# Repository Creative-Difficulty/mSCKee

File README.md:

# mSCKee

| | |
|-|-|

__msCKee__ is an open source split Keyboard with per-key white backlighting, and two light sensors, adapting to ambient brightness.

It features:
- dimmable white backlighting for every key, programmable to display animations
- two light sensors (one per side) to automatically dim backlight
- Integrated RP2040 MCU IC
- Minimalist aluminium enclosure
- USB-C 2.0 connectivity
- 4 layer board: Signal - GND - 3,3V and 5V split pour - Signal
- RJ9 cable connection between halves
- Cherry MX 5 pin switch compatible

All manufacturing and part costs were covered by Hack Club through their Outpost program (<https://outpost.hackclub.com>), which I am very grateful for.

Keycaps are custom from Hack Club for Outpost, product photos (top of the README) were taken in Vienna, Austria.

## BOM

The JLC BOM covers the majority of expenses:

Total cost of JLCPCB(A):

| Description | Price/Piece | Total Price | Purchase link | Justification |
|---|---|---|---|---|
| JLCPCB manufacturing and PCB assembly | 124.05€ + 22.72€ shipping | 146.77€ | | |
| Cherry MX Red Switch kit | 17.99€ + 11.99€ shipping | 29.98€ | https://shop.cherry.de/cherry-mx2a-rgb-red-switch-kit.html | |
| SP3T Switch: PCM13SMTR | 0.82€ | 5×0.82€ + 5.90€ shipping + 20% VAT = 12€ | https://www.tme.eu/at/details/pcm13smtr/schiebeschalter/c-k/ | No equivalent SP3T switch is available at JLC |
| 1N4148W7F DII SOD-123 diode | 0.05€ | 36×0.05€ + 6.95€ shipping + 20% VAT = 10.5€ | https://www.reichelt.com/at/en/shop/product/small-signal_switching_diode_100_v_300_ma_sod-123-219381 | Diodes for key matrix, mounted on back side of PCB, so not assembled or provided by JLC |
| **Total** | | **199.25€** | | |
| **Total (USD)** | | **232.59USD** | | |

## PCB & schematic images

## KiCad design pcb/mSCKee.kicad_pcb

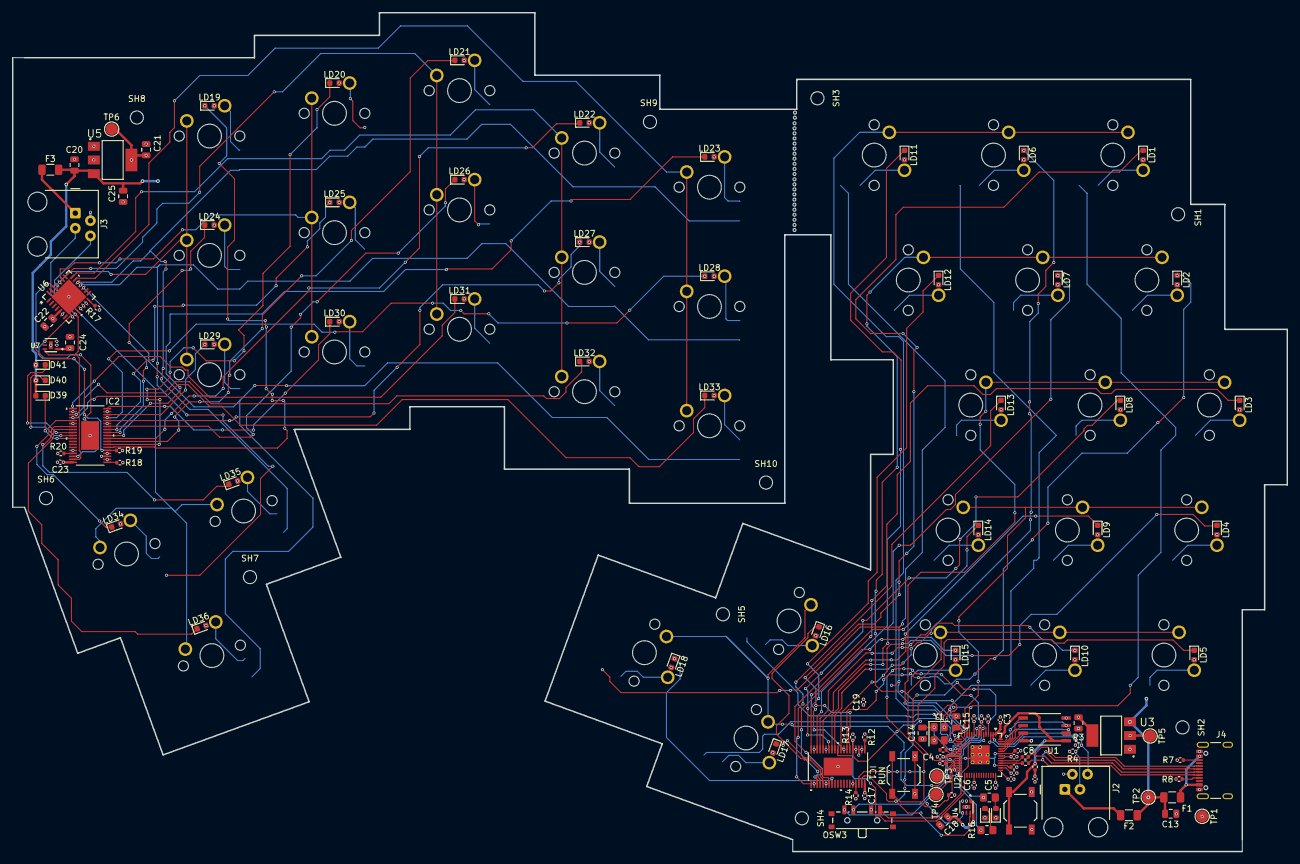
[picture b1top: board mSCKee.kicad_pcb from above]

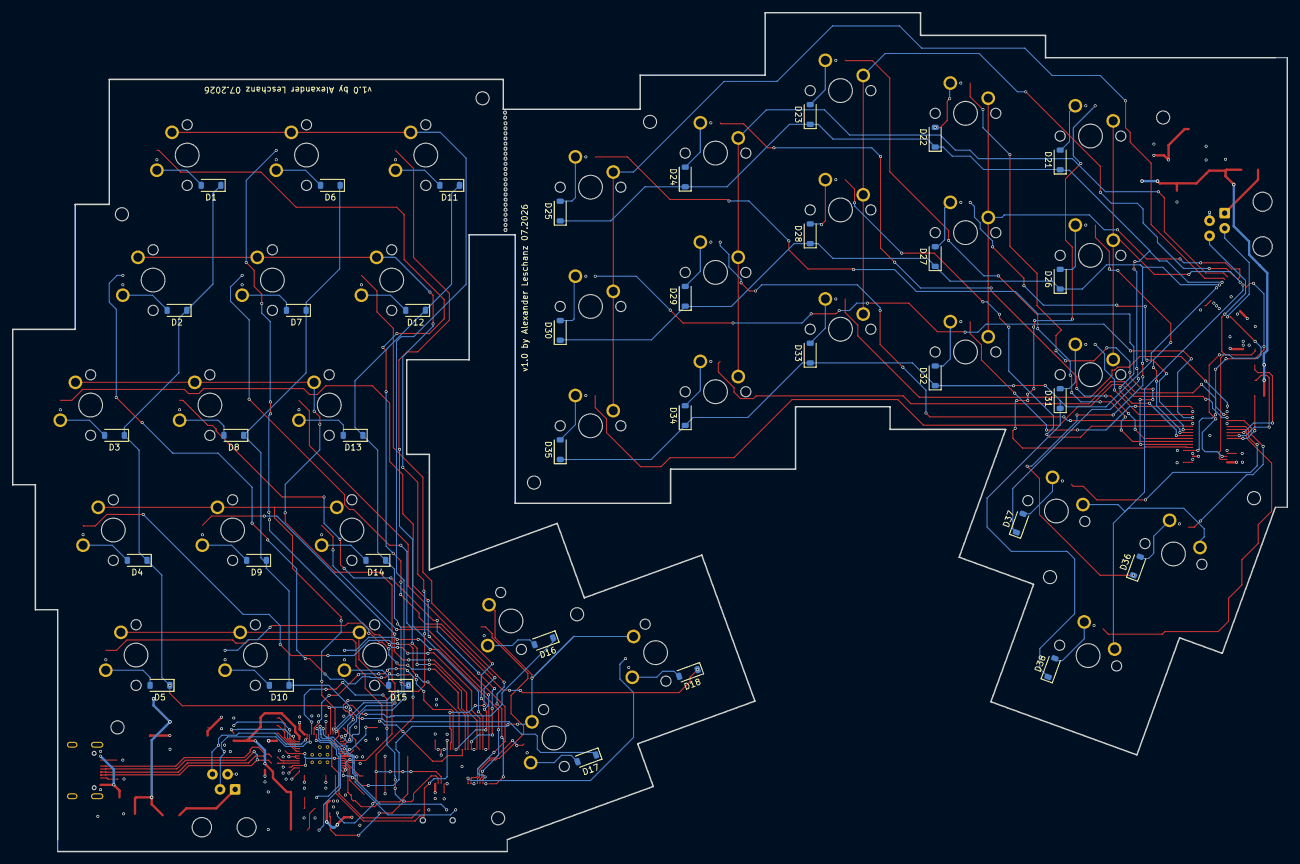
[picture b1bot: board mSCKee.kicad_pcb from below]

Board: 4 copper layers, 213.7 x 140.6 mm, 205 parts (36 on the bottom side), 141 nets.

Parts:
BL1, BL2: BreakLine_11h_D0.5mm_P0.85mm
BL3P, BL4P: (no value)
C1, C2, C3, C4, C5, C6, C7, C8, C9, C12, C17, C23: 100n; C_0402_1005Metric
C10, C11: 1u; C_0402_1005Metric
C13, C16, C20, C21, C25: 10u; C_0805_2012Metric
C14, C15: 15p; C_0805_2012Metric
C18, C22, C24: 100n; C_0805_2012Metric
C19: 10u; C_0402_1005Metric
D1, D2, D3, D4, D5, D6, D7, D8, D9, D10, D11, D12, D13, D14, D15, D16, D17, D18, D21, D22, D23, D24, D25, D26, D27, D28, D29, D30, D31, D32, D33, D34, D35, D36, D37, D38: D_Small; D_SOD-123
D19, D20: LED; LED_0603_1608Metric
D39, D40, D41: LED_Small; LED_0603_1608Metric
F1, F2, F3: Polyfuse_Small; Fuse_1206_3216Metric
IC1, IC2: PCA9956BTWY; HTSSOP38_4P4X9P7_NXP
J2, J3: 4P4C; RJ9_Evercom_5301-440xxx_Horizontal
J4: USB_C_Receptacle_USB2.0_16P; USB_C_Receptacle_GCT_USB4105-xx-A_16P_TopMnt_Horizontal
LD1, LD2, LD3, LD4, LD5, LD6, LD7, LD8, LD9, LD10, LD11, LD12, LD13, LD14, LD15, LD16, LD17, LD18, LD19, LD20, LD21, LD22, LD23, LD24, LD25, LD26, LD27, LD28, LD29, LD30, LD31, LD32, LD33, LD34, LD35, LD36: LED_Small; LED_0603_1608Metric
OSW1, OSW2: SW_Push; SW_SPST_TL3342
OSW3: SW_SP3T; SW_SP3T_PCM13
R1, R2: 27; R_0402_1005Metric
R3, R4: 2.2k; R_0402_1005Metric
R5, R6: 4.7k; R_0402_1005Metric
R7, R8: 5.1k; R_0402_1005Metric
R9, R10: 1k; R_0402_1005Metric
R11, R13, R14, R17, R19, R20: 10k; R_0402_1005Metric
R12, R18: 3k; R_0402_1005Metric
R15: 470; R_0805_2012Metric_Pad1.20x1.40mm_HandSolder
R16: 330; R_0805_2012Metric_Pad1.20x1.40mm_HandSolder
SH1, SH2, SH3, SH4, SH5, SH6, SH7, SH8, SH9, SH10: MountingHole_2.2mm_M2
SW1, SW2, SW3, SW4, SW5, SW6, SW7, SW8, SW9, SW10, SW11, SW12, SW13, SW14, SW15, SW16, SW17, SW18, SW19, SW20, SW21, SW22, SW23, SW24, SW25, SW26, SW27, SW28, SW29, SW30, SW31, SW32, SW33, SW34, SW35, SW36: SW_Push_45deg; MX-Solderable-1U
TP1, TP2, TP3, TP4, TP5, TP6: TestPoint; TestPoint_Pad_D2.0mm
TV2, TV3, TV4, TV5, TV6, TV7, TV8, TV9: (no value)
U1: W25Q128JVSIQ; SOIC127P790X216-8N
U2: RP2040; QFN-56-1EP_7x7mm_P0.4mm_EP3.2x3.2mm
U3, U5: NCP1117LPST33T3G; SOT230P700X175-4N
U4, U7: OPT3001DNPR; SON65P200X200X65-7N
U6: MCP23017T-E/ML; QFN28_6x6MC_MCH
Y1: ABM8-272-T3; Crystal_SMD_3225-4Pin_3.2x2.5mm

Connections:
+3V3: C1.1, C2.1, C3.1, C4.1, C5.1, C6.1, C7.1, C10.1, C12.2, C16.1, C17.1, C18.1, IC1.3 (AD1), IC1.38 (VDD), R3.1, R4.1, R5.1, R6.1, R9.1, R11.1, R13.2, R14.1, TP5.1 (1_1), U1.8 (VCC), U2.1 (IOVDD), U2.10 (IOVDD), U2.22 (IOVDD), U2.33 (IOVDD), U2.42 (IOVDD), U2.43 (ADC_AVDD), U2.44 (VREG_IN), U2.48 (USB_VDD), U2.49 (IOVDD), U3.2 (OUTPUT), U3.4 (OUTPUT__1), U4.1 (VDD)
+3V3_R: C21.1, C22.2, C23.2, C24.1, IC2.3 (AD1), IC2.38 (VDD), R17.1, R19.2, R20.1, TP6.1 (1_1), U5.2 (OUTPUT), U5.4 (OUTPUT__1), U6.5 (VDD), U7.1 (VDD)
+5V: C13.1, C19.1, F1.2, F2.1, LD1.2 (A), LD2.2 (A), LD3.2 (A), LD4.2 (A), LD5.2 (A), LD6.2 (A), LD7.2 (A), LD8.2 (A), LD9.2 (A), LD10.2 (A), LD11.2 (A), LD12.2 (A), LD13.2 (A), LD14.2 (A), LD15.2 (A), LD16.2 (A), LD17.2 (A), LD18.2 (A), TP2.1 (1_1), U3.3 (INPUT)
+5V_R: C20.1, C25.1, D39.2 (A), D40.2 (A), D41.2 (A), F3.2, LD19.2 (A), LD20.2 (A), LD21.2 (A), LD22.2 (A), LD23.2 (A), LD24.2 (A), LD25.2 (A), LD26.2 (A), LD27.2 (A), LD28.2 (A), LD29.2 (A), LD30.2 (A), LD31.2 (A), LD32.2 (A), LD33.2 (A), LD34.2 (A), LD35.2 (A), LD36.2 (A), U5.3 (INPUT)
/master_side/QSPI_SCLK: U1.6 (CLK), U2.52 (QSPI_SCLK)
/master_side/QSPI_SD0: U1.5 (DI(IO0)), U2.53 (QSPI_SD0)
/master_side/QSPI_SD1: U1.2 (DO(IO1)), U2.55 (QSPI_SD1)
/master_side/QSPI_SD2: U1.3 (/WP(IO2)), U2.54 (QSPI_SD2)
/master_side/QSPI_SD3: U1.7 (/HOLD/RESET(IO3)), U2.51 (QSPI_SD3)
/master_side/USB_D+: J4.A6 (D+), J4.B6 (D+), R1.1
/master_side/USB_D-: J4.A7 (D-), J4.B7 (D-), R2.1
/master_side/XIN: C14.1, U2.20 (XIN), Y1.1
/master_side/XOUT: R10.1, U2.21 (XOUT)
BL_DIM_1: OSW3.1, U2.8 (GPIO6)
BL_DIM_2: OSW3.2, U2.9 (GPIO7)
BL_DIM_3: OSW3.4, U2.11 (GPIO8)
COL0: SW1.1, SW6.1, SW11.1, U2.15 (GPIO12)
COL1: SW2.1, SW7.1, SW12.1, U2.16 (GPIO13)
COL2: SW3.1, SW8.1, SW13.1, U2.17 (GPIO14)
COL3: SW4.1, SW9.1, SW14.1, U2.18 (GPIO15)
COL4: SW5.1, SW10.1, SW15.1, U2.27 (GPIO16)
COL5: SW16.1, SW17.1, SW18.1, U2.28 (GPIO17)
COL6: SW34.1, SW35.1, SW36.1, U6.25 (GPB0)
COL7: SW19.1, SW24.1, SW29.1, U6.24 (GPA7)
COL8: SW20.1, SW25.1, SW30.1, U6.23 (GPA6)
COL9: SW21.1, SW26.1, SW31.1, U6.22 (GPA5)
COL10: SW22.1, SW27.1, SW32.1, U6.21 (GPA4)
COL11: SW23.1, SW28.1, SW33.1, U6.20 (GPA3)
GND: C1.2, C2.2, C3.2, C4.2, C5.2, C6.2, C7.2, C8.2, C9.2, C10.2, C11.2, C12.1, C13.2, C14.2, C15.2, C16.2, C17.2, C18.2, C19.2, D19.1 (K), D20.1 (K), IC1.2 (AD0), IC1.4 (AD2), IC1.14 (VSS), IC1.18 (VSS), IC1.21 (VSS), IC1.25 (VSS), IC1.34 (VSS), IC1.EPAD, J2.2, J4.A1 (GND), J4.A12 (GND), J4.B1 (GND), J4.B12 (GND), OSW1.1, OSW2.1, OSW3.3, R7.1, R8.1, R12.1, TP1.1 (1_1), TV2.101 (GND), TV3.102 (GND), TV4.103 (GND), TV5.104 (GND), TV6.105 (GND), TV7.106 (GND), TV8.107 (GND), TV9.108 (GND), U1.4 (GND), U2.19 (TESTEN), U2.57 (GND), U3.1 (GND), U4.2 (ADDR), U4.3 (GND), U4.7 (EXP), Y1.2, Y1.4
I2C_CLK: IC1.36 (SCL), R6.2, U2.5 (GPIO3), U4.4 (SCL)
I2C_CLK_R: J2.3, R4.2, U2.3 (GPIO1)
I2C_D: IC1.37 (SDA), R5.2, U2.4 (GPIO2), U4.6 (SDA)
I2C_D_R: J2.4, R3.2, U2.2 (GPIO0)
unnamed: C15.1, R10.2, Y1.3
unnamed: D3.2 (A), SW3.2
unnamed: D23.2 (A), SW21.2
unnamed: D4.2 (A), SW4.2
unnamed: D22.2 (A), SW20.2
unnamed: D5.2 (A), SW5.2
unnamed: D21.2 (A), SW19.2
unnamed: D2.2 (A), SW2.2
unnamed: D24.2 (A), SW22.2
unnamed: D1.2 (A), SW1.2
unnamed: D25.2 (A), SW23.2
unnamed: D8.2 (A), SW8.2
unnamed: D28.2 (A), SW26.2
unnamed: D9.2 (A), SW9.2
unnamed: D27.2 (A), SW25.2
unnamed: D10.2 (A), SW10.2
unnamed: D26.2 (A), SW24.2
unnamed: D7.2 (A), SW7.2
unnamed: D29.2 (A), SW27.2
unnamed: D19.2 (A), R15.2
unnamed: D20.2 (A), R16.2
unnamed: D6.2 (A), SW6.2
unnamed: D30.2 (A), SW28.2
unnamed: D13.2 (A), SW13.2
unnamed: D33.2 (A), SW31.2
unnamed: D14.2 (A), SW14.2
unnamed: D32.2 (A), SW30.2
unnamed: D15.2 (A), SW15.2
unnamed: D31.2 (A), SW29.2
unnamed: D12.2 (A), SW12.2
unnamed: D34.2 (A), SW32.2
unnamed: D11.2 (A), SW11.2
unnamed: D35.2 (A), SW33.2
unnamed: D16.2 (A), SW16.2
unnamed: D37.2 (A), SW35.2
unnamed: D17.2 (A), SW17.2
unnamed: D36.2 (A), SW34.2
unnamed: D18.2 (A), SW18.2
unnamed: D38.2 (A), SW36.2
unnamed: D39.1 (K), IC2.30 (LED20)
unnamed: D40.1 (K), IC2.29 (LED19)
unnamed: D41.1 (K), IC2.28 (LED18)
unnamed: F1.1, J4.A4 (VBUS), J4.A9 (VBUS), J4.B4 (VBUS), J4.B9 (VBUS)
unnamed: F2.2, J2.1
unnamed: F3.1, J3.1
unnamed: IC1.6 (LED0), LD1.1 (K)
unnamed: IC1.7 (LED1), LD2.1 (K)
unnamed: IC1.8 (LED2), LD3.1 (K)
unnamed: IC1.9 (LED3), LD4.1 (K)
unnamed: IC1.10 (LED4), LD5.1 (K)
unnamed: IC1.11 (LED5), LD6.1 (K)
unnamed: IC1.12 (LED6), LD7.1 (K)
unnamed: IC1.13 (LED7), LD8.1 (K)
unnamed: IC1.15 (LED8), LD9.1 (K)
unnamed: IC1.16 (LED9), LD10.1 (K)
unnamed: IC1.17 (LED10), LD11.1 (K)
unnamed: IC1.19 (LED11), LD12.1 (K)
unnamed: IC1.20 (LED12), LD13.1 (K)
unnamed: IC1.22 (LED13), LD14.1 (K)
unnamed: IC1.23 (LED14), LD15.1 (K)
unnamed: IC1.24 (LED15), LD16.1 (K)
unnamed: IC1.26 (LED16), LD17.1 (K)
unnamed: IC1.27 (LED17), LD18.1 (K)
unnamed: IC1.35 (RESET), R14.2
unnamed: IC1.1 (REXT), R12.2
unnamed: IC2.6 (LED0), LD19.1 (K)
unnamed: IC2.7 (LED1), LD20.1 (K)
unnamed: IC2.8 (LED2), LD21.1 (K)
unnamed: IC2.9 (LED3), LD22.1 (K)
unnamed: IC2.10 (LED4), LD23.1 (K)
unnamed: IC2.11 (LED5), LD24.1 (K)
unnamed: IC2.12 (LED6), LD25.1 (K)
unnamed: IC2.13 (LED7), LD26.1 (K)
unnamed: IC2.15 (LED8), LD27.1 (K)
unnamed: IC2.16 (LED9), LD28.1 (K)
unnamed: IC2.17 (LED10), LD29.1 (K)
unnamed: IC2.19 (LED11), LD30.1 (K)
unnamed: IC2.20 (LED12), LD31.1 (K)
unnamed: IC2.22 (LED13), LD32.1 (K)
unnamed: IC2.23 (LED14), LD33.1 (K)
unnamed: IC2.24 (LED15), LD34.1 (K)
unnamed: IC2.26 (LED16), LD35.1 (K)
unnamed: IC2.27 (LED17), LD36.1 (K)
unnamed: IC2.35 (RESET), R20.2
unnamed: IC2.1 (REXT), R18.2
unnamed: J4.A5 (CC1), R8.2
unnamed: J4.B5 (CC2), R7.2
unnamed: OSW2.2, R11.2, U2.26 (RUN)
unnamed: TP3.1 (1_1), U2.24 (SWCLK)
unnamed: TP4.1 (1_1), U2.25 (SWD)
unnamed: R2.2, U2.46 (USB_DM)
unnamed: R1.2, U2.47 (USB_DP)
unnamed: C8.1, C9.1, C11.1, U2.23 (DVDD), U2.45 (VREG_VOUT), U2.50 (DVDD)
unnamed: R17.2, U6.14 (*RESET)
OE_ENABLE: IC1.5 (OE), R13.1, U2.29 (GPIO18)
OE_ENABLE_R: IC2.5 (OE), R19.1, U6.26 (GPB1)
QSPI_SS: OSW1.2, R9.2, U1.1 (/CS), U2.56 (QSPI_SS)
ROW0: D1.1 (K), D2.1 (K), D3.1 (K), D4.1 (K), D5.1 (K), D16.1 (K), U2.12 (GPIO9)
ROW0_R: D21.1 (K), D22.1 (K), D23.1 (K), D24.1 (K), D25.1 (K), D37.1 (K), U6.19 (GPA2)
ROW1: D6.1 (K), D7.1 (K), D8.1 (K), D9.1 (K), D10.1 (K), D17.1 (K), U2.13 (GPIO10)
ROW1_R: D26.1 (K), D27.1 (K), D28.1 (K), D29.1 (K), D30.1 (K), D36.1 (K), U6.18 (GPA1)
ROW2: D11.1 (K), D12.1 (K), D13.1 (K), D14.1 (K), D15.1 (K), D18.1 (K), U2.14 (GPIO11)
ROW2_R: D31.1 (K), D32.1 (K), D33.1 (K), D34.1 (K), D35.1 (K), D38.1 (K), U6.17 (GPA0)
R_GND: C20.2, C21.2, C22.1, C23.1, C24.2, C25.2, IC2.2 (AD0), IC2.4 (AD2), IC2.14 (VSS), IC2.18 (VSS), IC2.21 (VSS), IC2.25 (VSS), IC2.34 (VSS), IC2.EPAD, J3.2, R18.1, U5.1 (GND), U6.6 (VSS), U6.11 (A0), U6.12 (A1), U6.13 (A2), U6.29 (HTAB), U7.2 (ADDR), U7.3 (GND), U7.7 (EXP)
STATUS1: R15.1, U2.6 (GPIO4)
STATUS2: R16.1, U2.7 (GPIO5)
S_M_CLOCK: IC2.36 (SCL), J3.3, U6.8 (SCL), U7.4 (SCL)
S_M_DATA: IC2.37 (SDA), J3.4, U6.9 (SDA), U7.6 (SDA)

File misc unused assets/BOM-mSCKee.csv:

Comment,Designator,Footprint,LCSC,Quantity
100n,"C1,C12,C17,C2,C3,C4,C5,C6,C7,C8,C9",C_0402_1005Metric,C1525,11
100n,C23,C_0402_1005Metric,C307331,1
100n,"C18,C22,C24",C_0805_2012Metric,C49678,3
10k,"R11,R13,R14,R17,R19,R20",R_0402_1005Metric,C60490,6
10u,C19,C_0402_1005Metric,C15525,1
10u,"C13,C16,C20,C21,C25",C_0805_2012Metric,C15850,5
15p,"C14,C15",C_0805_2012Metric,C107110,2
1k,"R10,R9",R_0402_1005Metric,C11702,2
1u,"C10,C11",C_0402_1005Metric,C52923,2
2.2k,"R3,R4",R_0402_1005Metric,C25879,2
27,"R1,R2",R_0402_1005Metric,C100353,2
330,R16,R_0805_2012Metric_Pad1.20x1.40mm_HandSolder,C17630,1
3k,"R12,R18",R_0402_1005Metric,C25559,2
4.7k,"R5,R6",R_0402_1005Metric,C25900,2
470,R15,R_0805_2012Metric_Pad1.20x1.40mm_HandSolder,C17710,1
4P4C,"J2,J3",RJ9_Evercom_5301-440xxx_Horizontal,C3097715,2
5.1k,"R7,R8",R_0402_1005Metric,C25905,2
ABM8-272-T3,Y1,Crystal_SMD_3225-4Pin_3.2x2.5mm,C20625731,1
D_Small,"D1,D10,D11,D12,D13,D14,D15,D16,D17,D18,D2,D21,D22,D23,D24,D25,D26,D27,D28,D29,D3,D30,D31,D32,D33,D34,D35,D36,D37,D38,D4,D5,D6,D7,D8,D9",D_SOD-123,C81598,36
LED,D20,LED_0603_1608Metric,C2286,1
LED,D19,LED_0603_1608Metric,C2290,1
LED_Small,"D39,D40,D41,LD1,LD10,LD11,LD12,LD13,LD14,LD15,LD16,LD17,LD18,LD19,LD2,LD20,LD21,LD22,LD23,LD24,LD25,LD26,LD27,LD28,LD29,LD3,LD30,LD31,LD32,LD33,LD34,LD35,LD36,LD4,LD5,LD6,LD7,LD8,LD9",LED_0603_1608Metric,C2290,39
MCP23017T-E/ML,U6,QFN28_6x6MC_MCH,C629439,1
NCP1117LPST33T3G,"U3,U5",SOT230P700X175-4N,C146799,2
OPT3001DNPR,"U4,U7",SON65P200X200X65-7N,C90462,2
PCA9956BTWY,"IC1,IC2",HTSSOP38_4P4X9P7_NXP,C2678558,2
Polyfuse_Small,"F1,F2,F3",Fuse_1206_3216Metric,C545217,3
RP2040,U2,QFN-56-1EP_7x7mm_P0.4mm_EP3.2x3.2mm,C2040,1
SW_Push,"OSW1,OSW2",SW_SPST_TL3342,C2886894,2
USB_C_Receptacle_USB2.0_16P,J4,USB_C_Receptacle_GCT_USB4105-xx-A_16P_TopMnt_Horizontal,C3020560,1
W25Q128JVSIQ,U1,SOIC127P790X216-8N,C97521,1
TestPoint,TP5,TestPoint_Pad_D2.0mm,,1
TestPoint,TP4,TestPoint_Pad_D2.0mm,,1
TestPoint,TP3,TestPoint_Pad_D2.0mm,,1
TestPoint,TP1,TestPoint_Pad_D2.0mm,,1
TestPoint,TP2,TestPoint_Pad_D2.0mm,,1
TestPoint,TP6,TestPoint_Pad_D2.0mm,,1

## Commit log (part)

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2025-10-31 chore: Add usb-c to README
2025-10-31 chore: delete license
2025-11-02 feat: init KiCad project & add RP2040
2025-11-02 chore: update description in README
2025-11-13 chore: Reinit and readd RP2040 minimal circuit
2025-11-13 feat(schematic): Connect crystal and flash chip to RP2040
2025-11-14 feat(schematic): Wire up USB-C receptacle
2025-11-14 chore: Update README
2025-11-17 feat(schematic): Add GPIO connection labels and an LED to one
2025-12-19 misc: Add keep QSPI conn short
2026-01-29 feat: Add TRRS receptacle and split sheets into master & slave side
2026-01-31 Add TRRS connector, rotary encoder, ambient light sensor
2026-02-01 Restructure file & folder layout
2026-02-02 update readme
    Added a section for current progress with an image.
2026-02-23 feat: Add more components, add finalized outline
2026-03-01 feat: Add both sides of outline in CAD
2026-03-25 feat: Further develop right side
2026-03-25 fix: left/right nets separation
2026-03-26 feat: Replace PCA9555 with MCP23017
2026-03-27 fix: I2C pullups on both buses
2026-03-27 fix: Proper MX LED footprint
2026-03-27 fix: revert to proper switch footprint without SMD LED
2026-03-28 fix: OE pin PCA9956B control on startup
2026-03-30 fix: PCA9956 OE pin and RESET pin and improve LED power delivery
2026-03-31 fix: Diode & switch numbering for kbplacer
2026-03-31 fix: Update points to be both sides of keyboard
    Diode numbers don't match though
2026-03-31 feat: Better global label names
2026-03-31 fix: Proper USB-C receptacle symbol
2026-06-02 fix: Fix thumb cluster key splay & Correctly align keys to outline in PCB layout
2026-06-02 chore(for future reference): Properly lay out keys, keep components unrouted
2026-06-04 fix(broken): Reroute USB
    TODO:
    - Fix 0402 imperial and metric confusion
    - Fix DRC errors (are holes of claws of USB-C and ethernet big enough to manufacture?)
    - Proper decoupling cap distribution between pins
    - Manage the +1.1V and +3.3V situation (maybe create +1.1V net)
2026-06-05 feat: Improve layout & route crystal and flash
2026-06-25 feat: Add NC flags to both side schematics
2026-06-25 feat: Add I2C left side pullups, move status LED resistors to backside
2026-06-27 feat: Route switches amongst themselves & Remove weirdly behaving netclass sizes
    TODO: route LD's and figure out how to connect them all to the driver (put driver IC on back side of board?)
2026-06-30 chore: Restructure Journal (import from fallout) for outpost
2026-06-30 chore: Fix up journal, add total running hour count
2026-06-30 feat: Route master-side LEDs to driver
    TODO route matrix on thumb cluster master side
